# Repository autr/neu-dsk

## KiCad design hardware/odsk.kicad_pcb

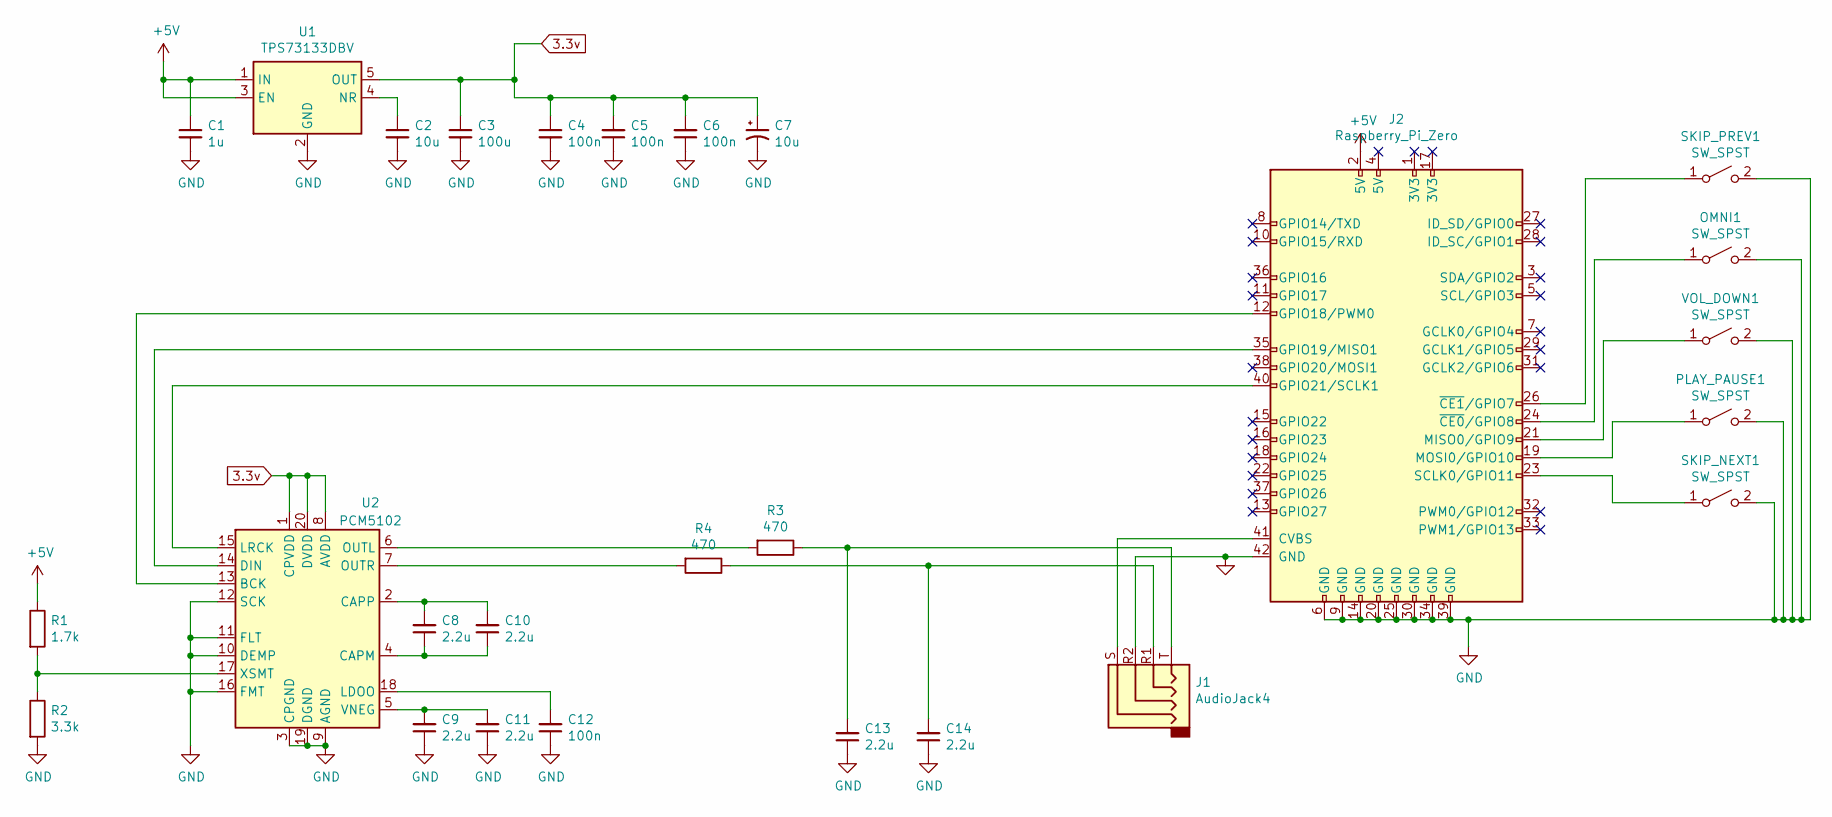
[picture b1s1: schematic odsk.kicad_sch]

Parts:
C1: 1u; C_0805_2012Metric_Pad1.18x1.45mm_HandSolder
C2: 10u; C_0805_2012Metric_Pad1.18x1.45mm_HandSolder
C3: 100u; C_1206_3216Metric_Pad1.33x1.80mm_HandSolder
C4, C5, C6, C12: 100n; C_0805_2012Metric_Pad1.18x1.45mm_HandSolder
C7: 10u; CP_Elec_5x5.4
C8, C9, C10, C11, C13, C14: 2.2u; C_0805_2012Metric_Pad1.18x1.45mm_HandSolder
J1: AudioJack4; TRRS-PJ-320A-Jack
J2: Raspberry_Pi_Zero
OMNI1: SW_SPST; SW_Tactile_SPST_Angled_PTS645Vx39-2LFS
PLAY_PAUSE1: SW_SPST; SW_Tactile_SPST_Angled_PTS645Vx39-2LFS
R1: 1.7k; R_0805_2012Metric_Pad1.20x1.40mm_HandSolder
R2: 3.3k; R_0805_2012Metric_Pad1.20x1.40mm_HandSolder
R3, R4: 470; R_0805_2012Metric_Pad1.20x1.40mm_HandSolder
SKIP_NEXT1: SW_SPST; SW_Tactile_SPST_Angled_PTS645Vx39-2LFS
SKIP_PREV1: SW_SPST; SW_Tactile_SPST_Angled_PTS645Vx39-2LFS
U1: TPS73133DBV; SOT-23-5
U2: PCM5102; TSSOP-20_4.4x6.5mm_P0.65mm
VOL_DOWN1: SW_SPST; SW_Tactile_SPST_Angled_PTS645Vx39-2LFS

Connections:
3.3v: C3.1, C4.1, C5.2, C6.2, C7.1, U1.5 (OUT), U2.1 (CPVDD), U2.8 (AVDD), U2.20 (DVDD)
+5V: C1.1, J2.2 (5V), R1.1, U1.1 (IN), U1.3 (EN)
unnamed: C2.1, U1.4 (NR)
unnamed: C8.1, C10.1, U2.4 (CAPM)
unnamed: C8.2, C10.2, U2.2 (CAPP)
unnamed: C9.2, C11.2, U2.5 (VNEG)
unnamed: C12.2, U2.18 (LDOO)
unnamed: C13.2, J1.T, R3.1
unnamed: C14.2, J1.R1, R4.1
unnamed: J1.S, J2.41 (CVBS)
unnamed: J2.12 (GPIO18/PWM0), U2.13 (BCK)
unnamed: J2.19 (MOSI0/GPIO10), PLAY_PAUSE1.1 (A)
unnamed: J2.21 (MISO0/GPIO9), VOL_DOWN1.1 (A)
unnamed: J2.23 (SCLK0/GPIO11), SKIP_NEXT1.1 (A)
unnamed: J2.24 (~CE0/GPIO8), OMNI1.1 (A)
unnamed: J2.26 (~CE1/GPIO7), SKIP_PREV1.1 (A)
unnamed: J2.35 (GPIO19/MISO1), U2.14 (DIN)
unnamed: J2.40 (GPIO21/SCLK1), U2.15 (LRCK)
unnamed: R1.2, R2.1, U2.17 (XSMT)
unnamed: R3.2, U2.6 (OUTL)
unnamed: R4.2, U2.7 (OUTR)

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
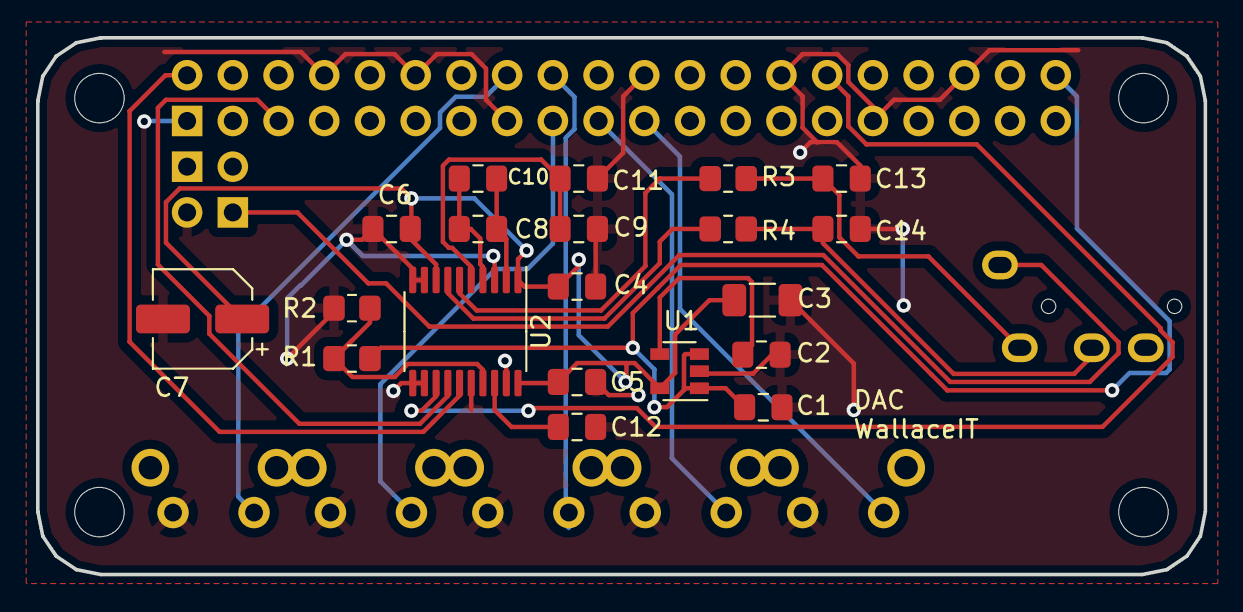
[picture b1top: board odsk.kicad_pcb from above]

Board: 2 copper layers, 64.9 x 29.8 mm, 27 parts (0 on the bottom side), 22 nets.

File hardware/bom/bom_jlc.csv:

Comment,Designator,Footprint,LCSC
1u,C1,Capacitor_SMD:C_0805_2012Metric_Pad1.18x1.45mm_HandSolder,C28323
10u,C2,Capacitor_SMD:C_0805_2012Metric_Pad1.18x1.45mm_HandSolder,C15850
100u,C3,Capacitor_SMD:C_1206_3216Metric_Pad1.33x1.80mm_HandSolder,C15008
100n,"C4,C5,C6,C12",Capacitor_SMD:C_0805_2012Metric_Pad1.18x1.45mm_HandSolder,C28233
10u,C7,Capacitor_SMD:CP_Elec_5x5.4,C335978
2.2u,"C8,C9,C10,C11,C13,C14",Capacitor_SMD:C_0805_2012Metric_Pad1.18x1.45mm_HandSolder,C49217
AudioJack4,J1,lib_fb:TRRS-PJ-320A-Jack,
Raspberry_Pi_Zero,J2,lib_fb:Raspberry_Pi_Zero,
1.7k,R1,Resistor_SMD:R_0805_2012Metric_Pad1.20x1.40mm_HandSolder,C17395
3.3k,R2,Resistor_SMD:R_0805_2012Metric_Pad1.20x1.40mm_HandSolder,C26010
470,"R3,R4",Resistor_SMD:R_0805_2012Metric_Pad1.20x1.40mm_HandSolder,C17710
SW_SPST,"SKIP_PREV1,OMNI1,VOL_DOWN1,PLAY_PAUSE1,SKIP_NEXT1,VOL_UP1",Button_Switch_THT:SW_Tactile_SPST_Angled_PTS645Vx39-2LFS,
TPS73133DBV,U1,Package_TO_SOT_SMD:SOT-23-5,C515169
PCM5102,U2,Package_SO:TSSOP-20_4.4x6.5mm_P0.65mm,

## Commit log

2021-06-30 init
2021-06-30 fix pins mixup, emojis, finalise
2021-07-08 finalise
2021-07-08 sync with 3b+ src
2021-07-08 custom.txt
2021-07-08 faster switching zero
2021-07-26 tweak
2021-07-26 messages
2021-08-24 refactor and organise
2021-08-24 fix paths
2021-08-24 optimised
2021-08-25 disable keyboard (todo: try/catch)
2021-08-25 reorganise, fix bugs
2022-04-05 add jlc pcba files
2022-04-05 remove unused files
2022-04-12 update cap footprint
2022-04-19 gpio numbering & labels
2022-04-25 typos
2022-05-18 jlc bom
2022-07-06 [V2.2] Swap TRRS R1/R2, connect 5V, CVBS GND, reposition buttons
